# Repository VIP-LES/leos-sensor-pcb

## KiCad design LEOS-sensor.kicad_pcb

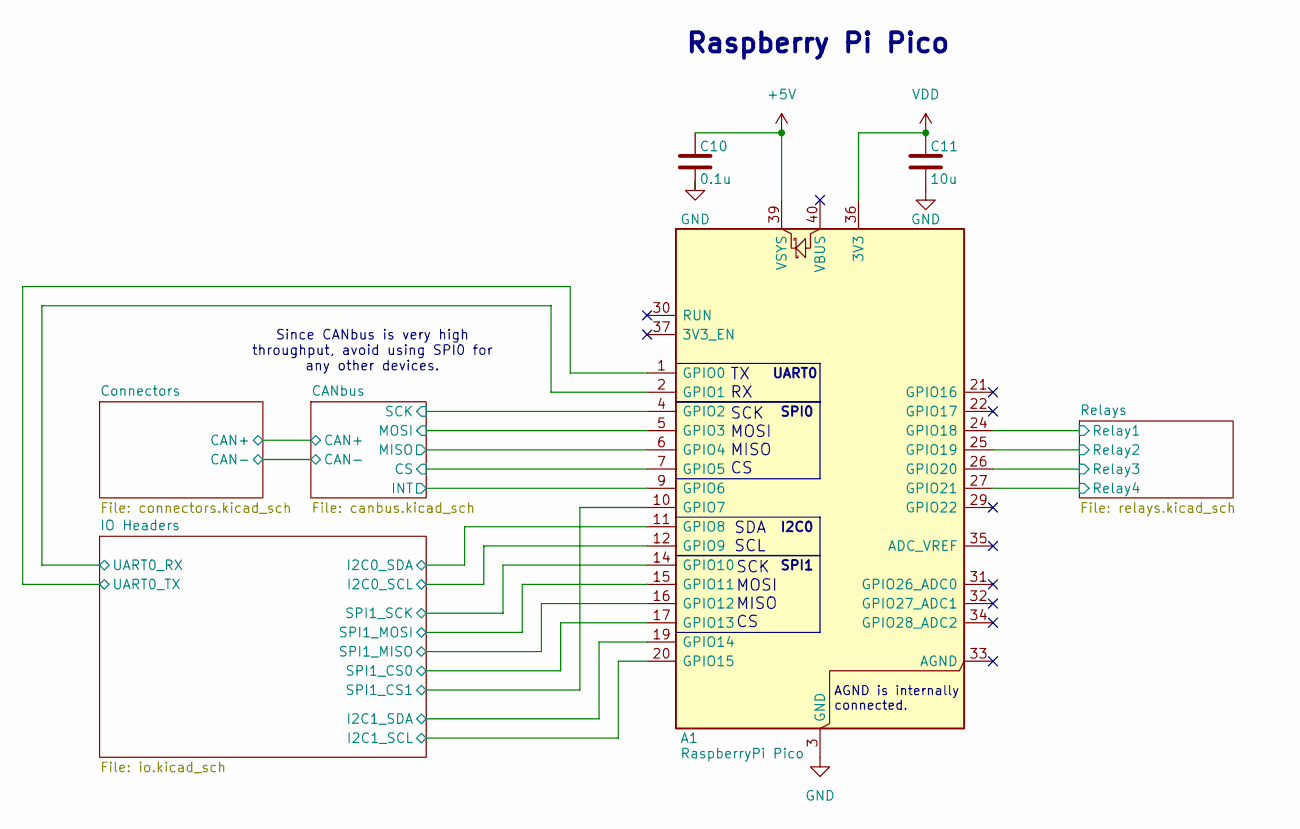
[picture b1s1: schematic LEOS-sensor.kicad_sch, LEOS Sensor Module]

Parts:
A1: RaspberryPi Pico; RaspberryPi_Pico_Common_THT; MPN PIM724; Digikey 1778-PIM724-ND
C10: 0.1u; C_0603_1608Metric; MPN CL10B104KB8NNNL; Digikey 1276-CL10B104KB8NNNLCT-ND
C11: 10u; C_0805_2012Metric; MPN CL21B106KOQNNNE; Digikey 1276-2872-1-ND

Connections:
+5V: A1.39 (VSYS), C10.1; also elsewhere on the board
/CANbus/CS: A1.7 (GPIO5); also elsewhere on the board
/CANbus/INT: A1.9 (GPIO6); also elsewhere on the board
/CANbus/MISO: A1.6 (GPIO4); also elsewhere on the board
/CANbus/MOSI: A1.5 (GPIO3); also elsewhere on the board
/CANbus/SCK: A1.4 (GPIO2); also elsewhere on the board
/IO Headers/I2C0_SCL: A1.12 (GPIO9); also elsewhere on the board
/IO Headers/I2C0_SDA: A1.11 (GPIO8); also elsewhere on the board
/IO Headers/I2C1_SCL: A1.20 (GPIO15); also elsewhere on the board
/IO Headers/I2C1_SDA: A1.19 (GPIO14); also elsewhere on the board
/IO Headers/SPI1_CS0: A1.17 (GPIO13); also elsewhere on the board
/IO Headers/SPI1_CS1: A1.10 (GPIO7); also elsewhere on the board
/IO Headers/SPI1_MISO: A1.16 (GPIO12); also elsewhere on the board
/IO Headers/SPI1_MOSI: A1.15 (GPIO11); also elsewhere on the board
/IO Headers/SPI1_SCK: A1.14 (GPIO10); also elsewhere on the board
/IO Headers/UART0_RX: A1.2 (GPIO1); also elsewhere on the board
/IO Headers/UART0_TX: A1.1 (GPIO0); also elsewhere on the board
/Relays/Relay1: A1.24 (GPIO18); also elsewhere on the board
/Relays/Relay2: A1.25 (GPIO19); also elsewhere on the board
/Relays/Relay3: A1.26 (GPIO20); also elsewhere on the board
/Relays/Relay4: A1.27 (GPIO21); also elsewhere on the board
GND: A1.3 (GND), A1.8 (GND), A1.13 (GND), A1.18 (GND), A1.23 (GND), A1.28 (GND), A1.38 (GND), C10.2, C11.2; also elsewhere on the board
VDD: A1.36 (3V3), C11.1; also elsewhere on the board

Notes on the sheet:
SPI1
Raspberry Pi Pico
SCK MOSI MISO CS
Since CANbus is very high throughput, avoid using SPI0 for any other devices.
SPI0
SDA SCL
TX RX
UART0
I2C0
AGND is internally connected.

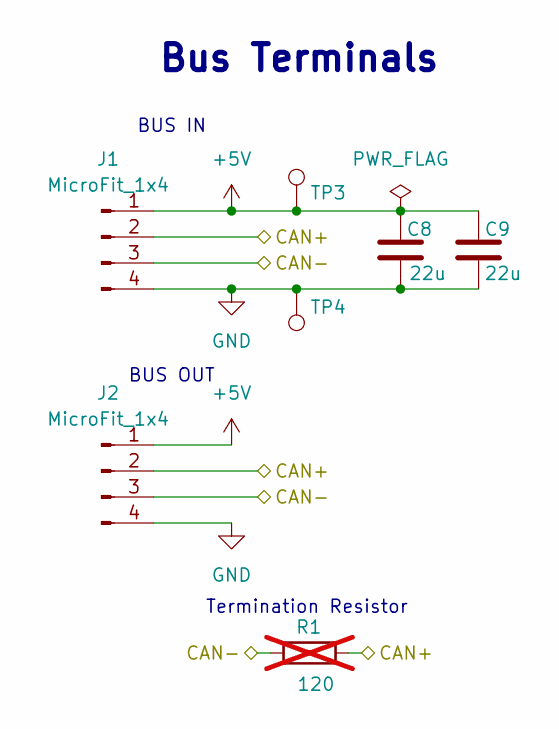
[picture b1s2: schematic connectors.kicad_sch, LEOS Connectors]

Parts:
C8, C9: 22u; C_0805_2012Metric; MPN CL21A226MAYNNNE; Digikey 1276-CL21A226MAYNNNECT-ND
J1, J2: MicroFit_1x4; Molex_MicroFit3.0_43650-0410_1x04_Horizontal; MPN 0436500409; Digikey WM1882CT-ND
R1: 120; R_Axial_DIN0207_L6.3mm_D2.5mm_P7.62mm_Horizontal; MPN CF14JT120R; Digikey CF14JT120RCT-ND; not fitted
TP3: 5V Test Point; TestPoint_Loop_D2.60mm_Drill0.9mm_Beaded; MPN 5000; Digikey 36-5000-ND
TP4: GND Test Point; TestPoint_Loop_D2.60mm_Drill0.9mm_Beaded; MPN 5001; Digikey 36-5001-ND

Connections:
+5V: C8.1, C9.1, J1.1, J2.1, TP3.1; also elsewhere on the board
/CANbus/CAN+: J1.2, J2.2, R1.2; also elsewhere on the board
/CANbus/CAN-: J1.3, J2.3, R1.1; also elsewhere on the board
GND: C8.2, C9.2, J1.4, J2.4, TP4.1; also elsewhere on the board

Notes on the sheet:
BUS OUT
Bus Terminals
BUS IN
Termination Resistor

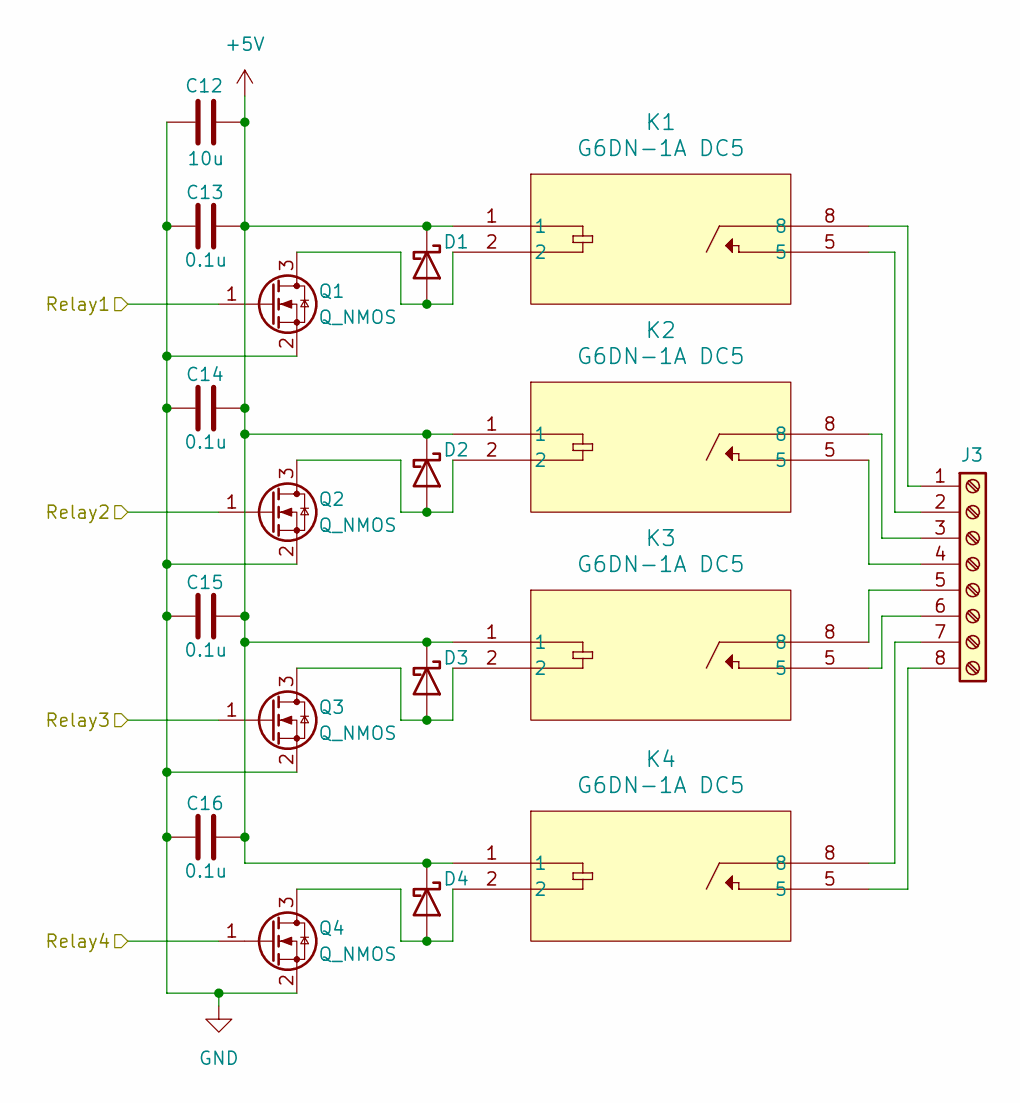
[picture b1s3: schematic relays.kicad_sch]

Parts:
C12: 10u; C_0805_2012Metric; MPN CL21B106KOQNNNE; LCSC C95841
C13, C14, C15, C16: 0.1u; C_0603_1608Metric; MPN CL10B104KB8NNNL; LCSC C913912
D1, D2, D3, D4: D_Schottky; D_SMA; MPN SS14; LCSC C83852
J3: Screw_Terminal_01x08; TerminalBlock_Phoenix_MKDS-1,5-8-5.08_1x08_P5.08mm_Horizont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; MPN 1715789; Digikey 277-1266-ND
K1, K2, K3, K4: G6DN-1A DC5; RELAY_G6DN-1A_OMR; MPN G6DN-1A DC5; Digikey 39-G6DN-1ADC5-ND
Q1, Q2, Q3, Q4: Q_NMOS; SOT-23; MPN IRLML0030TRPBF; LCSC C67272

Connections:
+5V: C12.2, C13.1, C14.1, C15.1, C16.1, D1.1 (K), D2.1 (K), D3.1 (K), D4.1 (K), K1.1, K2.1, K3.1, K4.1; also elsewhere on the board
/Relays/Relay1: Q1.1 (G); also elsewhere on the board
/Relays/Relay2: Q2.1 (G); also elsewhere on the board
/Relays/Relay3: Q3.1 (G); also elsewhere on the board
/Relays/Relay4: Q4.1 (G); also elsewhere on the board
GND: C12.1, C13.2, C14.2, C15.2, C16.2, Q1.2 (S), Q2.2 (S), Q3.2 (S), Q4.2 (S); also elsewhere on the board
unnamed: D1.2 (A), K1.2, Q1.3 (D)
unnamed: D2.2 (A), K2.2, Q2.3 (D)
unnamed: D3.2 (A), K3.2, Q3.3 (D)
unnamed: D4.2 (A), K4.2, Q4.3 (D)
unnamed: J3.1, K1.8
unnamed: J3.2, K1.5
unnamed: J3.3, K2.8
unnamed: J3.4, K2.5
unnamed: J3.5, K3.8
unnamed: J3.6, K3.5
unnamed: J3.7, K4.8
unnamed: J3.8, K4.5

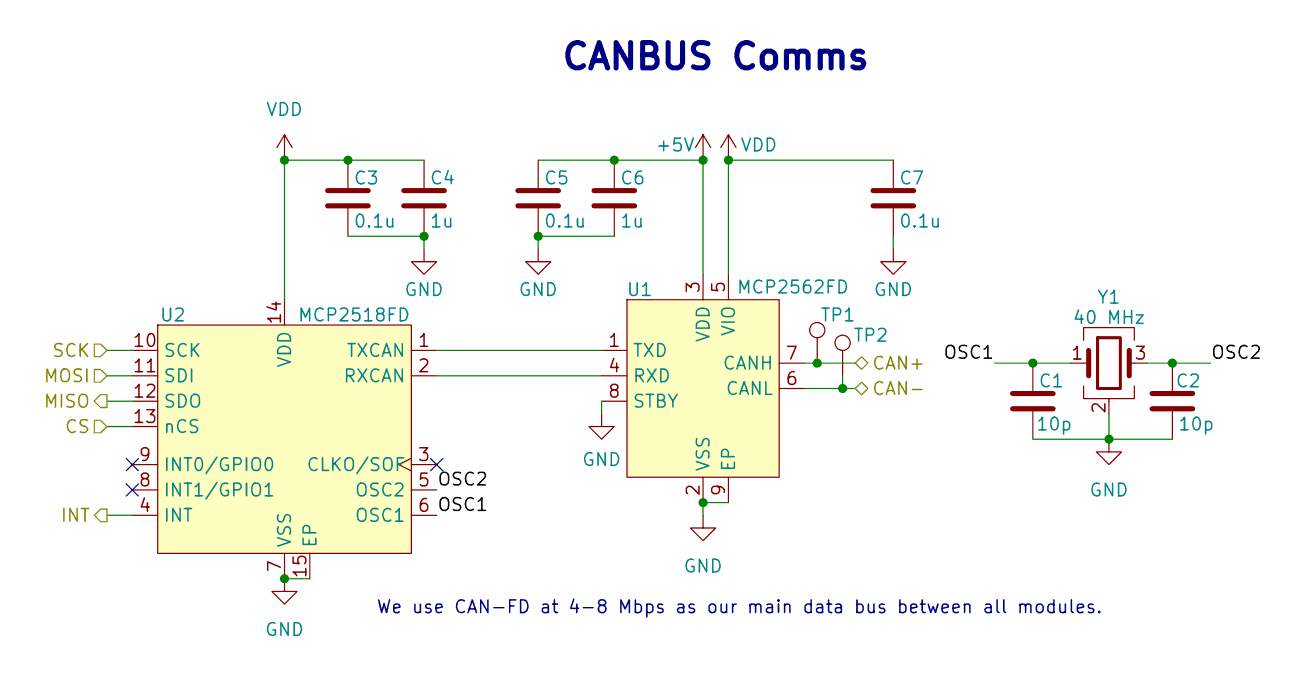
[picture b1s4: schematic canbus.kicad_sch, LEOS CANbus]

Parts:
C1, C2: 10p; C_0603_1608Metric; MPN CL10C100JB8NNNC; Digikey 1276-1027-1-ND
C3, C5, C7: 0.1u; C_0603_1608Metric; MPN CL10B104KB8NNNL; Digikey 1276-CL10B104KB8NNNLCT-ND
C4, C6: 1u; C_0603_1608Metric; MPN CL10B105KA8NNNC; Digikey 1276-1184-1-ND
TP1: CAN-H Test Point; TestPoint_Loop_D2.60mm_Drill0.9mm_Beaded; MPN 5004; Digikey 36-5004-ND
TP2: CAN-L Test Point; TestPoint_Loop_D2.60mm_Drill0.9mm_Beaded; MPN 5116; Digikey 36-5116-ND
U1: MCP2562FD; SOIC-8_3.9x4.9mm_P1.27mm; MPN MCP2562FDT-H/SN; LCSC C511335
U2: MCP2518FD; SOIC-14_3.9x8.7mm_P1.27mm; MPN MCP2518FDT-E/SL; LCSC C626758
Y1: 40 MHz; Crystal_SMD_2016-4Pin_2.0x1.6mm; MPN ECS-400-10-37B2-CKY-TR; Digikey 50-ECS-400-10-37B2-CKY-TRCT-ND

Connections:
+5V: C5.1, C6.1, U1.3 (VDD); also elsewhere on the board
/CANbus/CAN+: TP1.1, U1.7 (CANH); also elsewhere on the board
/CANbus/CAN-: TP2.1, U1.6 (CANL); also elsewhere on the board
/CANbus/CS: U2.13 (nCS); also elsewhere on the board
/CANbus/INT: U2.4 (INT); also elsewhere on the board
/CANbus/MISO: U2.12 (SDO); also elsewhere on the board
/CANbus/MOSI: U2.11 (SDI); also elsewhere on the board
/CANbus/OSC1: C1.2, U2.6 (OSC1), Y1.1
/CANbus/OSC2: C2.2, U2.5 (OSC2), Y1.3
/CANbus/SCK: U2.10 (SCK); also elsewhere on the board
GND: C1.1, C2.1, C3.2, C4.2, C5.2, C6.2, C7.2, U1.2 (VSS), U1.8 (STBY), U1.9 (EP), U2.7 (VSS), U2.15 (EP), Y1.2 (G), Y1.4 (G); also elsewhere on the board
unnamed: U1.4 (RXD), U2.2 (RXCAN)
unnamed: U1.1 (TXD), U2.1 (TXCAN)
VDD: C3.1, C4.1, C7.1, U1.5 (VIO), U2.14 (VDD); also elsewhere on the board

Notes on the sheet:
CANBUS Comms
We use CAN-FD at 4-8 Mbps as our main data bus between all modules.

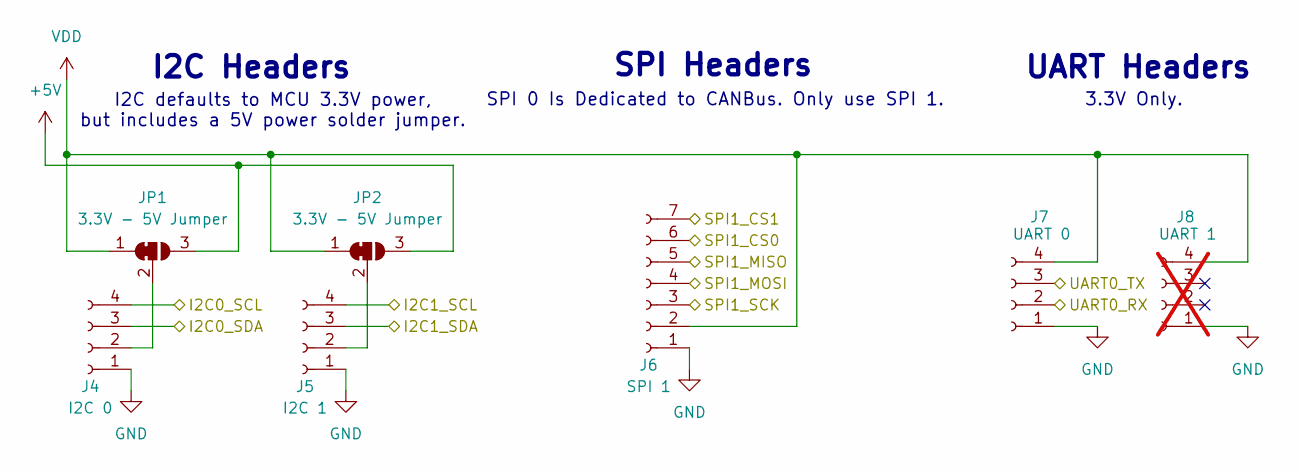
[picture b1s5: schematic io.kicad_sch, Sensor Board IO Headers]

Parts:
J4: I2C 0; JST_XH_S4B-XH-A_1x04_P2.50mm_Horizontal; MPN S4B-XH-A; Digikey 455-2243-ND
J5: I2C 1; JST_XH_S4B-XH-A_1x04_P2.50mm_Horizontal; MPN S4B-XH-A; Digikey 455-2243-ND
J6: SPI 1; JST_XH_S7B-XH-A_1x07_P2.50mm_Horizontal; MPN S7B-XH-A; Digikey 455-S7B-XH-A-ND
J7: UART 0; JST_XH_S4B-XH-A_1x04_P2.50mm_Horizontal; MPN S4B-XH-A; Digikey 455-2243-ND
J8: UART 1; JST_XH_S4B-XH-A_1x04_P2.50mm_Horizontal; MPN S4B-XH-A; Digikey 455-2243-ND; not fitted
JP1, JP2: 3.3V - 5V Jumper; SolderJumper-3_P1.3mm_Bridged12_RoundedPad1.0x1.5mm

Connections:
+5V: JP1.3 (B), JP2.3 (B); also elsewhere on the board
/IO Headers/I2C0_SCL: J4.4; also elsewhere on the board
/IO Headers/I2C0_SDA: J4.3; also elsewhere on the board
/IO Headers/I2C1_SCL: J5.4; also elsewhere on the board
/IO Headers/I2C1_SDA: J5.3; also elsewhere on the board
/IO Headers/SPI1_CS0: J6.6; also elsewhere on the board
/IO Headers/SPI1_CS1: J6.7; also elsewhere on the board
/IO Headers/SPI1_MISO: J6.5; also elsewhere on the board
/IO Headers/SPI1_MOSI: J6.4; also elsewhere on the board
/IO Headers/SPI1_SCK: J6.3; also elsewhere on the board
/IO Headers/UART0_RX: J7.2; also elsewhere on the board
/IO Headers/UART0_TX: J7.3; also elsewhere on the board
GND: J4.1, J5.1, J6.1, J7.1, J8.1; also elsewhere on the board
unnamed: J4.2, JP1.2 (C)
unnamed: J5.2, JP2.2 (C)
VDD: J6.2, J7.4, J8.4, JP1.1 (A), JP2.1 (A); also elsewhere on the board

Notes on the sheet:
3.3V Only.
SPI Headers
SPI 0 Is Dedicated to CANBus. Only use SPI 1.
UART Headers
I2C defaults to MCU 3.3V power, but includes a 5V power solder jumper.
I2C Headers

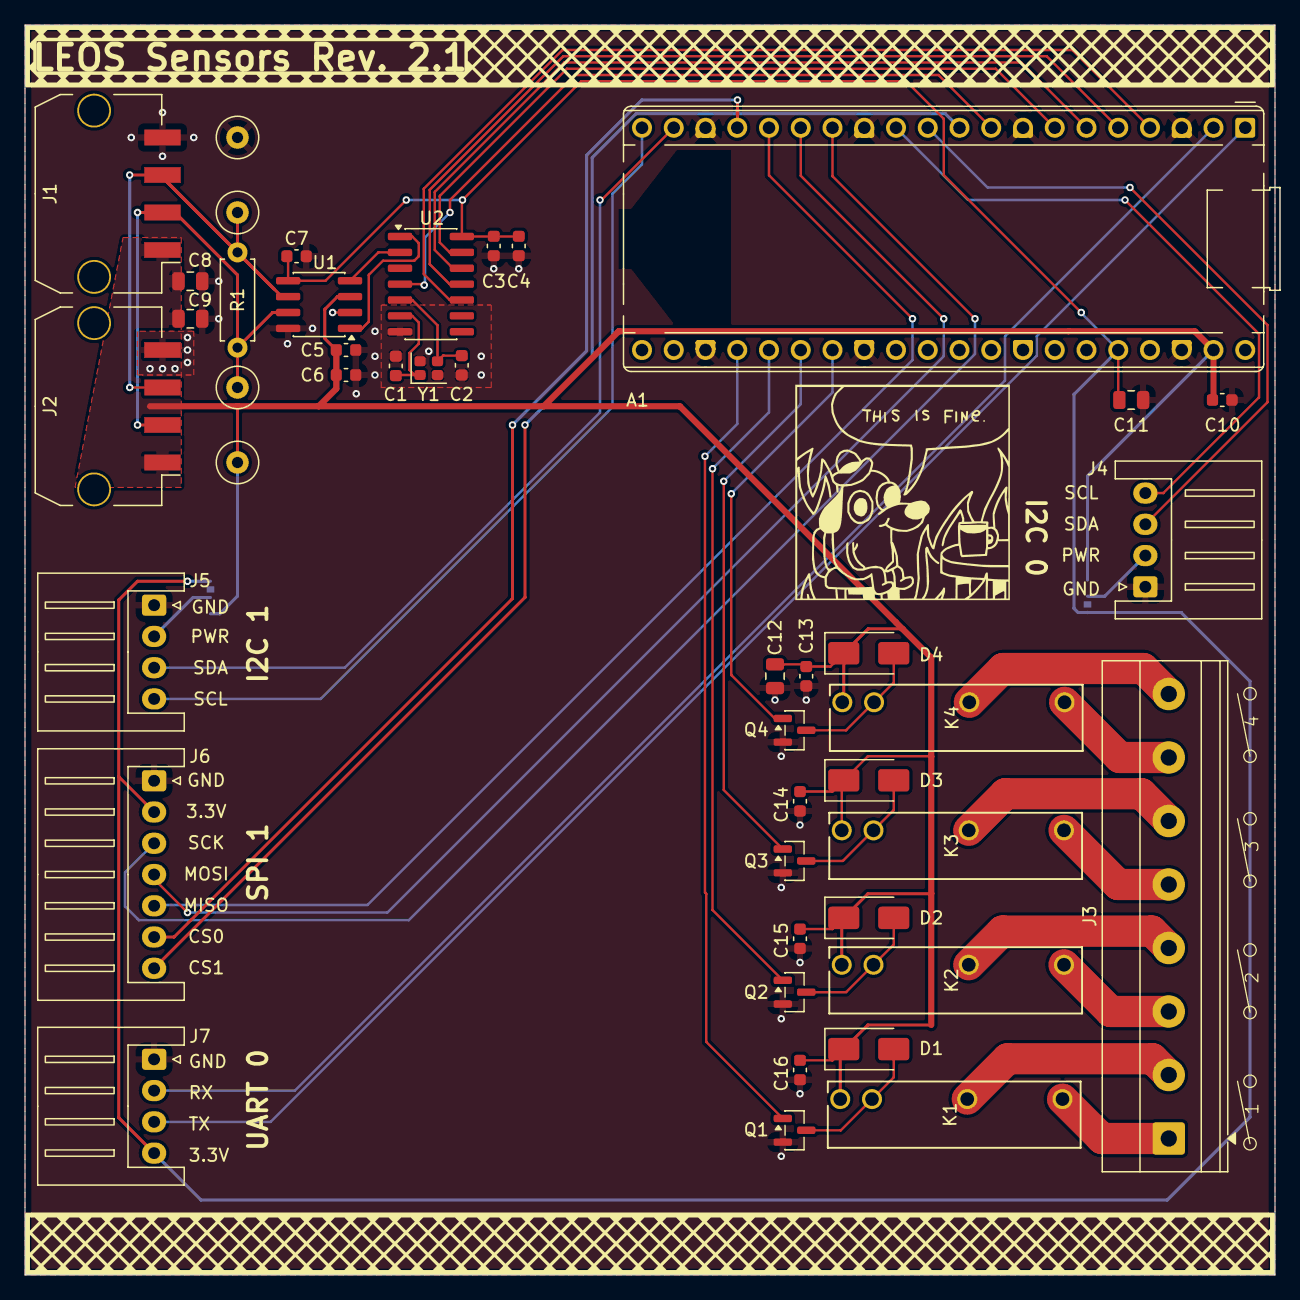
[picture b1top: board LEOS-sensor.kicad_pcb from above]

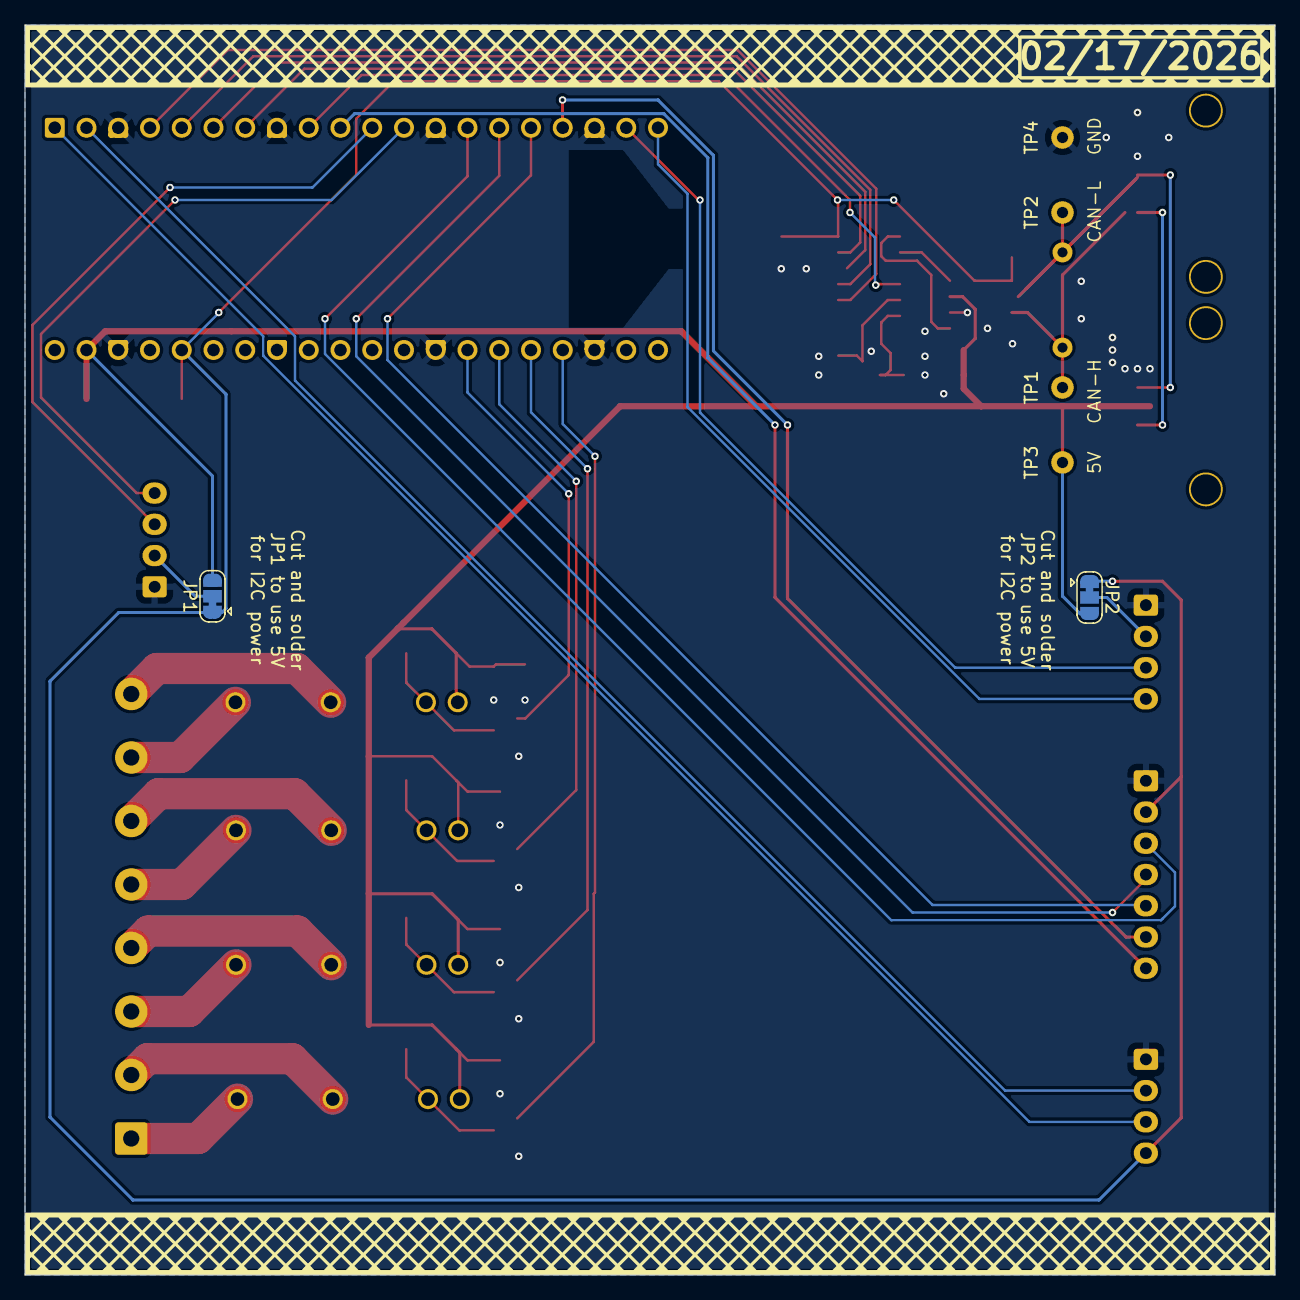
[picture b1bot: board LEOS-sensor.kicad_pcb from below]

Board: 2 copper layers, 100.0 x 100.0 mm, 46 parts (2 on the bottom side), 43 nets.

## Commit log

2026-02-16 Updated from template, added graphics and JST-XH connectors
2026-02-17 Add production date and up revision
2026-02-17 Add default output for STEP file
2026-02-17 Add .gitignore for KiCad and backup files
